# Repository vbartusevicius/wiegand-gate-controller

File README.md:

# Wiegand Gate Controller (`wiegand-gate-controller`)

Compact **ESP32-C6** Wiegand access-control gateway for sliding/swing gates and doors — connects standard 12 V Wiegand card/UHF/keypad readers to gate controllers, door strikes, maglocks, and **Home Assistant** over Wi-Fi/MQTT.

## Enclosure & Hardware (`v1`)

*3D-printed enclosure (`78.8 × 58.8 × 27.7 mm`) with engraved terminal labels and translucent `0.4 mm` status LED windows.*

| 4-Layer PCB — Top (`74.0 × 54.0 mm`) | 4-Layer PCB — Bottom |
| :---: | :---: |
|  |  |

- **9–32 V DC input (`PWR`)**: polyfuse, reverse-polarity diode, TVS clamp, ADC supply monitor, and dual step-down converters (`+5 V` logic + fused `+12 V` reader/aux supply).
- **Wiegand reader port (`WIEGAND`)**: 5 V-tolerant Schmitt-buffered `D0`/`D1`, open-drain `LED`/`BEEP` outputs, supports auto-detected 26/34/37/58-bit cards and 4/8-bit keypad PINs.
- **2× isolated relays (`RELAY 1`, `RELAY 2`)**: potential-free Form-C dry contacts (`2 A / 30 V DC` max) for Open/Close, Step/Pedestrian, or Dual-Door control.
- **3× opto-isolated inputs (`SENSORS`, `EXIT / 12V`)**: accept 5–24 V DC signals or dry contacts (magnetic reed, dual limits, controller blinking status output, and exit/REX pushbutton).
- **Tool-free WAGO 2086 SMD push-in terminals** (`J1`–`J5`, 3.5 mm pitch) + **Seeed XIAO ESP32-C6** (built-in antenna + optional external stickable U.FL antenna via `ANT` exit slot with automatic firmware RSSI selection), dual `WS2812B` RGB LEDs (`NET`, `GATE`), and `RST` button behind a `0.4 mm` translucent cover window.

## Web UI & Home Assistant

### Overview & Live I/O

### Visual Gate Setup & Terminal Map

### Firmware OTA & Maintenance

- **Standalone local access control**: stores up to 500 users/cards/PINs on flash with one-click enrollment of the last unknown scanned tag.
- **Visual setup**: tap how a card read operates your gate/door and how open/closed position is sensed; the live terminal diagram updates to match the labels engraved on the box.
- **Separated Network & OTA pages**: dedicated Wi-Fi + MQTT / Home Assistant auto-discovery tab (`cover` / `lock`, `binary_sensor`, `sensor`, `button`) and drag-and-drop `firmware.bin` OTA updates (gzip-embedded Web UI updates atomically with firmware).

## Enclosure Terminal Map

| Edge | Box Group | Pins | Function |
| :--- | :--- | :--- | :--- |
| Bottom | `PWR` | `V+`, `GND` | 9–32 V DC input |
| Bottom | `WIEGAND` | `12V`, `GND`, `D0`, `D1`, `LED`, `BEEP` | 12 V Wiegand reader & keypad |
| Top | `RELAY 1` | `NC`, `NO`, `COM` | Primary relay dry contact |
| Top | `RELAY 2` | `NC`, `NO`, `COM` | Secondary / Close / Pedestrian relay |
| Top | `SENSORS` | `IN2-`, `IN2+`, `IN1-`, `IN1+` | Position / limit / status inputs |
| Top | `EXIT / 12V` | `GND`, `+12V`, `IN3-`, `IN3+` | Exit (REX) input & +12 V wetting supply |
| Left | `USB` | USB-C | Initial flashing & serial console |
| Right | `ANT` | U.FL coax slot | Optional external 2.4 GHz stickable antenna exit |

## Documentation

- [Wiring & Controller Integration Guide](docs/wiring.md)
- [PCB, BOM & 3D Enclosure Ordering Guide](docs/ordering.md)

## Quick Build & Verification (Docker-first)

```bash
# Python lint
docker compose --profile lint run --rm -T lint check .

# Firmware native & sanitized unit tests + ESP32-C6 release image
docker compose --profile lint run --rm -T cpp-lint "pio test -d firmware -e native && pio test -d firmware -e native_sanitized"
python3 firmware/scripts/release_firmware.py

# Hardware PCB DRC/connectivity + JLCPCB release + tests
docker compose --profile hardware run --rm -T -e JLC_LIVE=0 eda "python3 hardware/scripts/release.py v1 && python3 -m pytest hardware/tests -q -p no:cacheprovider"

# Mechanical enclosure build + tests
docker compose --profile hardware run --rm -T cad "python3 hardware/scripts/build.py --in-cad --test"

# Package GitHub Release bundle (hardware zip + firmware bins + SHA256SUMS.txt + release table)
python3 scripts/package_release.py
```

## License

See [LICENSE.md](LICENSE.md).

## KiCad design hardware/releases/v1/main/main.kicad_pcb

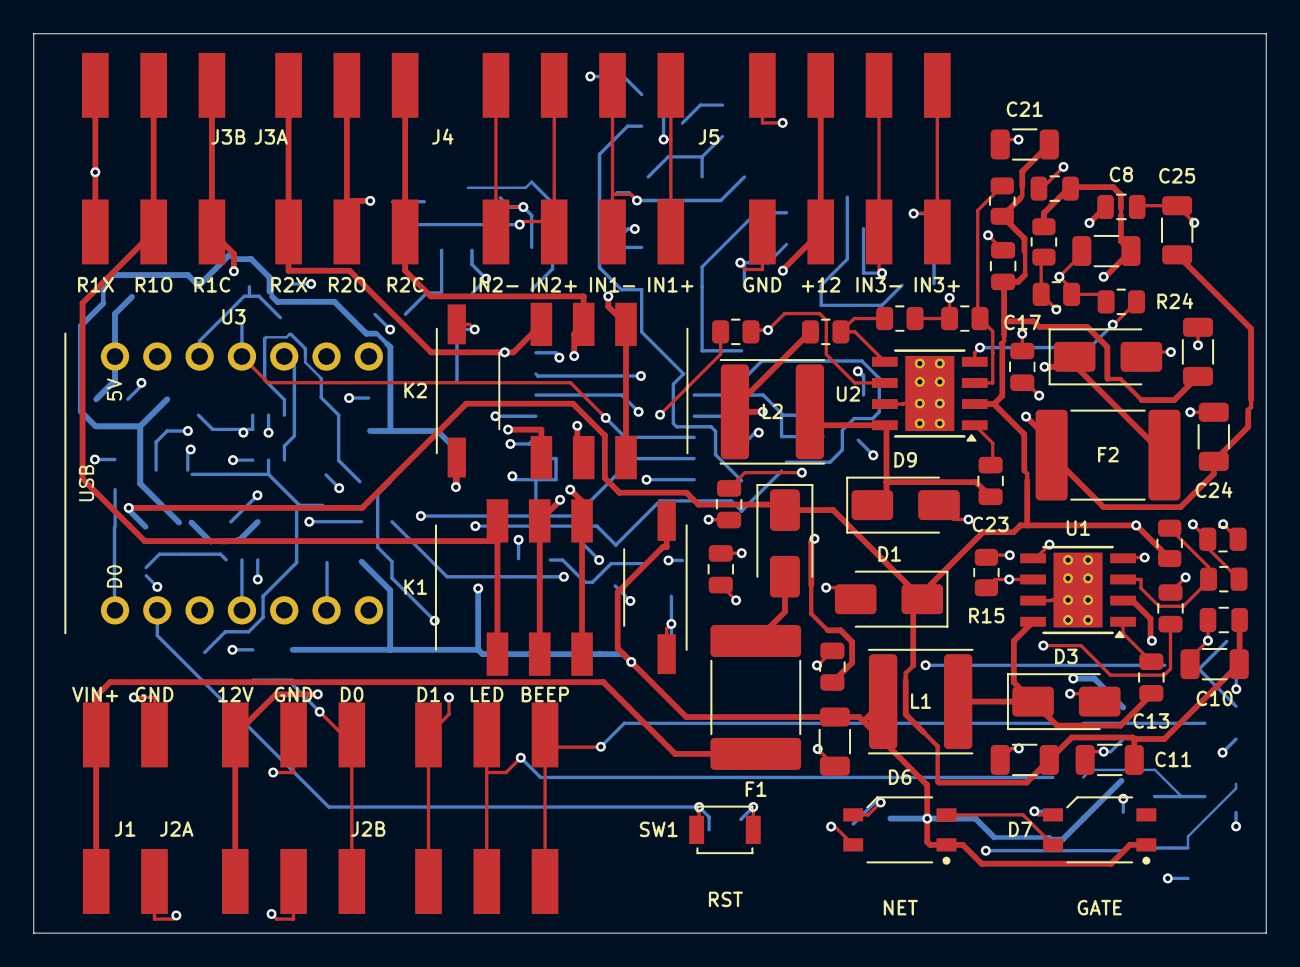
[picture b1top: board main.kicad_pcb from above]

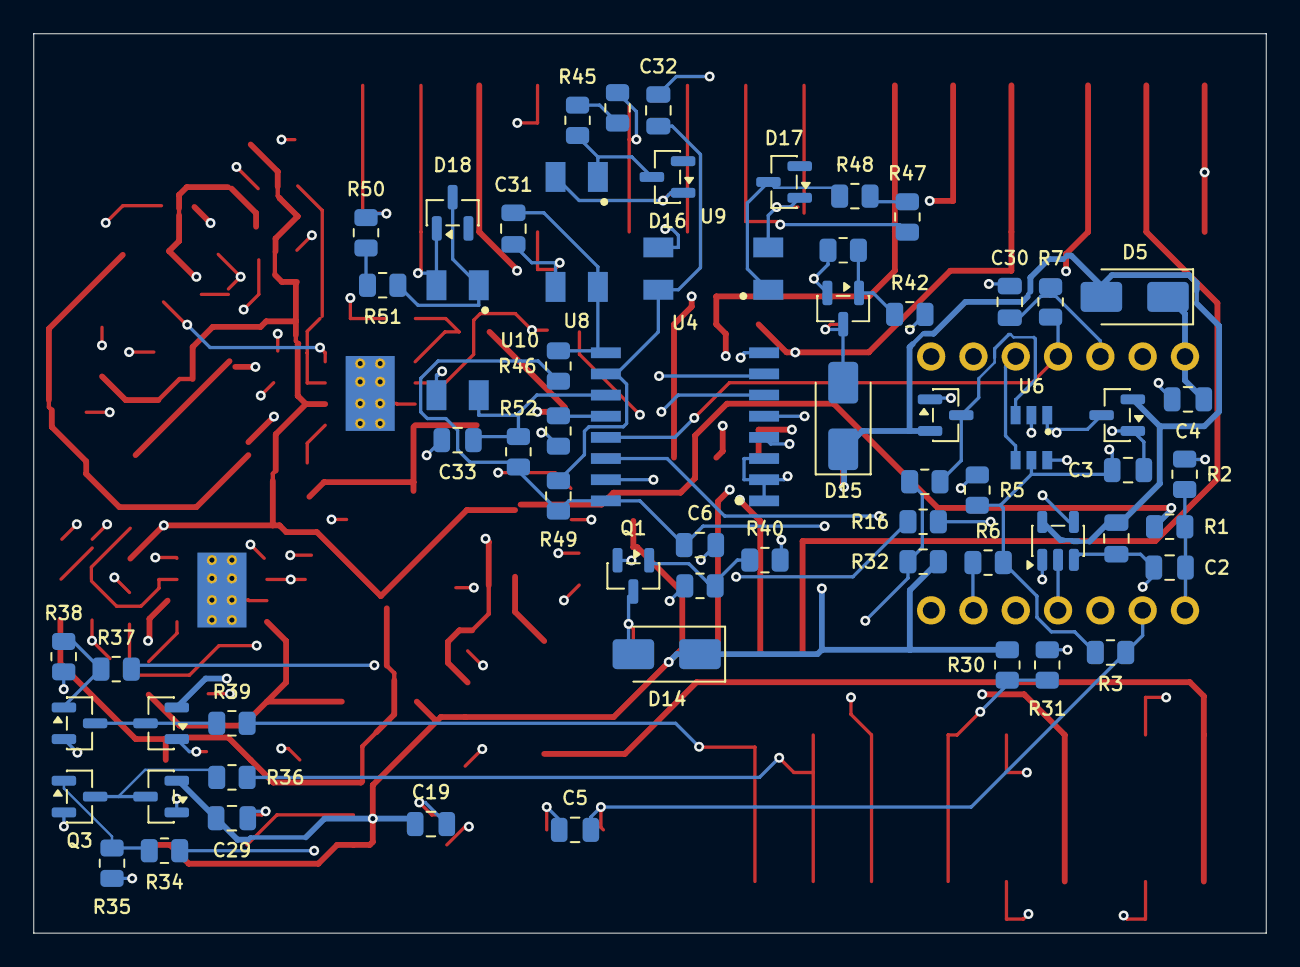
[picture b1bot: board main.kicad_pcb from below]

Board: 4 copper layers, 74.0 x 54.0 mm, 119 parts (63 on the bottom side), 74 nets.

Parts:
C1, C10, C11, C20, C21: 2u2 100V; C_1206_3216Metric
C2, C5, C6, C8, C9, C13, C16, C19, C23, C26, C29, C30, C31, C32, C33: 100n 50V; C_0805_2012Metric
C3, C4: 10u 10V; C_0805_2012Metric
C12, C22: 100n 100V; C_0805_2012Metric
C14, C15: 47u 10V; C_1206_3216Metric
C17: 33n 50V; C_0805_2012Metric
C18, C28: 68p C0G 50V; C_0805_2012Metric
C24, C25: 22u 25V; C_1206_3216Metric
C27: 18n 50V; C_0805_2012Metric
D1: SMAJ36A; D_SMA
D2: SS36; D_SMA
D3, D9: B360A; D_SMA
D5, D14, D15: SS14; D_SMA
D6, D7: WS2812B-MINI-V3J; LED_WS2812B-MINI-V3J
D8: SMAJ15A; D_SMA
D10, D11, D12, D13, D16, D17, D18: BAT54S; SOT-23
F1, F2: 1.1A; Fuse_2920_7451Metric
J1: PWR; TerminalBlock_WAGO_2086-1202_SMD
J2A: WIEGAND_A; TerminalBlock_WAGO_2086-1203_SMD
J2B: WIEGAND_B; TerminalBlock_WAGO_2086-1203_SMD
J3A: RELAY_1; TerminalBlock_WAGO_2086-1203_SMD
J3B: RELAY_2; TerminalBlock_WAGO_2086-1203_SMD
J4: SENSE_1_2; TerminalBlock_WAGO_2086-1204_SMD
J5: SENSE_3_AUX; TerminalBlock_WAGO_2086-1204_SMD
K1, K2: G6S-2F DC5; Relay_DPDT_Omron_G6S-2F_2A
L1: 8.2uH; L_Sunlord_SWPA6045S
L2: 22uH; L_Sunlord_SWPA6045S
Q1, Q2, Q3, Q4: MMBT3904; SOT-23
R1: 100k; R_0805_2012Metric
R2, R3, R4, R7, R23, R30, R32, R35, R38, R41, R43, R46, R49, R52: 10k; R_0805_2012Metric
R5, R6, R44, R45, R47, R48, R50, R51: 2k2; R_0805_2012Metric
R10, R20: 511k; R_0805_2012Metric
R11, R21: 82k5; R_0805_2012Metric
R12, R15, R25: 53k6; R_0805_2012Metric
R13: 10k2; R_0805_2012Metric
R14, R24: 130k; R_0805_2012Metric
R16, R31, R33, R36, R39: 330R; R_0805_2012Metric
R22: 140k; R_0805_2012Metric
R34, R37: 1k; R_0805_2012Metric
R40, R42: 470R; R_0805_2012Metric
SW1: RESTART; SW_SPST_B3U-1000P
U1, U2: TPS54360DDAR; TI_SO-PowerPAD-8_ThermalVias
U3: XIAO ESP32C6; XIAO_ESP32C6_Header
U4: TCA9534DWR; TI_TCA9534DWR_SOIC-16
U5: 74AHCT1G125; SOT-23-5
U6: SN74LVC2G17; TI_SN74LVC2G17_SOT-23-6
U8, U9, U10: EL357N; Everlight_EL357N_SOP-4

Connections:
5V_BST: C13.1, U1.1
5V_CC: C17.1, R15.2
5V_COMP: C18.1, R15.1, U1.6
5V_EN: R10.2, R11.1, U1.3
5V_FB: R12.2, R13.1, U1.5
5V_RT: R14.1, U1.4
5V_SW: C13.2, D3.1, L1.1, U1.8
12V_BST: C23.1, U2.1
12V_CC: C27.1, R25.2
12V_COMP: C28.1, R25.1, U2.6
12V_EN: R20.2, R21.1, U2.3
12V_FB: R22.2, R23.1, U2.5
12V_RT: R24.1, U2.4
12V_SW: C23.2, D9.1, L2.1, U2.8
+3V3: C3.1, C6.1, C30.1, R3.1, R5.1, R6.1, R7.1, R46.1, R49.1, R52.1, U3.12, U4.16, U6.5
+5V: C9.1, C14.1, C15.1, C16.1, C19.1, C29.1, D5.2, D6.1, D7.1, D10.2, D11.2, D12.2, D13.2, D14.1, D15.1, K1.1, K2.1, L1.2, R12.1, R30.1, R32.1, U5.5
+5V_XIAO: C4.1, D5.1, U3.14
+12V_RDR: C24.1, C25.1, C26.1, F2.1, L2.2, R22.1
+12V_RDR_OUT: C8.1, D8.1, F2.2, J2A.1, J5.3
BTN_RESTART: C5.1, R3.2, SW1.1, U3.2
EXP_INT: R7.2, U3.11, U4.13
EXP_P7: R4.1, U4.12
GND: C1.2, C2.2, C3.2, C4.2, C5.2, C6.2, C8.2, C9.2, C10.2, C11.2, C12.2, C14.2, C15.2, C16.2, C17.2, C18.2, C19.2, C20.2, C21.2, C22.2, C24.2, C25.2, C26.2, C27.2, C28.2, C29.2, C30.2, C31.2, C32.2, C33.2, D1.2, D3.2, D6.3, D7.3, D8.2, D9.2, D10.1, D11.1, D12.1, D13.1, J1.2, J2A.2, J5.4, Q1.2, Q2.2, Q3.2, Q4.2, R2.2, R4.2, R11.2, R13.2, R14.2, R21.2, R23.2, R24.2, R35.2, R38.2, R41.2, R43.2, SW1.2, U1.7, U1.9, U2.7, U2.9, U3.13, U4.1, U4.2, U4.3, U4.8, U5.1, U5.3, U6.2, U8.3, U9.3, U10.3
I2C_SCL: R6.2, U3.6, U4.14
I2C_SDA: R5.2, U3.5, U4.15
IN1_LED_A: D16.3, R45.2, U8.1
IN1_MCU: C31.1, R46.2, U4.9, U8.4
IN1_MID: R44.2, R45.1
IN1_N: D16.1, J4.2, U8.2
IN1_P: J4.1, R44.1
IN2_LED_A: D17.3, R48.2, U9.1
IN2_MCU: C32.1, R49.2, U4.10, U9.4
IN2_MID: R47.2, R48.1
IN2_N: D17.1, J4.4, U9.2
IN2_P: J4.3, R47.1
IN3_LED_A: D18.3, R51.2, U10.1
IN3_MCU: C33.1, R52.2, U4.11, U10.4
IN3_MID: R50.2, R51.1
IN3_N: D18.1, J5.2, U10.2
IN3_P: J5.1, R50.1
LED_BUF: R16.1, U5.4
LED_CHAIN1: D6.2, D7.4
LED_DATA: U3.4, U5.2
LED_DIN: D6.4, R16.2
R1_BASE: Q1.1, R40.2, R41.1
R1_COIL_N: D14.2, K1.12, Q1.3
R1_COM: J3A.1, K1.4, K1.9
R1_NC: J3A.3, K1.3, K1.10
R1_NO: J3A.2, K1.5, K1.8
R2_BASE: Q2.1, R42.2, R43.1
R2_COIL_N: D15.2, K2.12, Q2.3
R2_COM: J3B.1, K2.4, K2.9
R2_NC: J3B.3, K2.3, K2.10
R2_NO: J3B.2, K2.5, K2.8
RELAY1_DRV: R40.1, U4.4
RELAY2_DRV: R42.1, U4.5
VIN_ADC: C2.1, R1.2, R2.1, U3.1
VIN_FUSED: D2.2, F1.2
VIN_PROT: C1.1, C10.1, C11.1, C12.1, C20.1, C21.1, C22.1, D1.1, D2.1, R1.1, R10.1, R20.1, U1.2, U2.2
VIN_RAW: F1.1, J1.1
WG_BEEP_BASE: Q4.1, R37.2, R38.1
WG_BEEP_COL: D13.3, Q4.3, R39.1
WG_BEEP_DRV: R37.1, U4.7
WG_BEEP_TERM: J2B.3, R39.2
WG_D0_IN: D10.3, R31.2, U6.1
WG_D0_MCU: U3.3, U6.6
WG_D0_TERM: J2A.3, R30.2, R31.1
WG_D1_IN: D11.3, R33.2, U6.3
WG_D1_MCU: U3.10, U6.4
WG_D1_TERM: J2B.1, R32.2, R33.1
WG_LED_BASE: Q3.1, R34.2, R35.1
WG_LED_COL: D12.3, Q3.3, R36.1
WG_LED_DRV: R34.1, U4.6
WG_LED_TERM: J2B.2, R36.2

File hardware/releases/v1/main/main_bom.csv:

Line,Qty,Designators,Value,Package,Type,Manufacturer,MPN,LCSC,Assembly
1,5,"C1,C10,C11,C20,C21",2u2 100V,C_1206_3216Metric,SMD,Samsung,CL31B225KCHSNNE,C170101,machine
2,2,"C12,C22",100n 100V,C_0805_2012Metric,SMD,YAGEO,CC0805KKX7R0BB104,C106243,machine
3,15,"C13,C16,C19,C2,C23,C26,C29,C30,C31,C32,C33,C5,C6,C8,C9",100n 50V,C_0805_2012Metric,SMD,YAGEO,CC0805KRX7R9BB104,C49678,machine
4,2,"C14,C15",47u 10V,C_1206_3216Metric,SMD,Samsung,CL31A476MPHNNNE,C96123,machine
5,1,C17,33n 50V,C_0805_2012Metric,SMD,YAGEO,CC0805KRX7R9BB333,C107150,machine
6,2,"C18,C28",68p C0G 50V,C_0805_2012Metric,SMD,YAGEO,CC0805JRNPO9BN680,C107120,machine
7,2,"C24,C25",22u 25V,C_1206_3216Metric,SMD,Samsung,CL31A226KAHNNNE,C12891,machine
8,1,C27,18n 50V,C_0805_2012Metric,SMD,YAGEO,CC0805JRX7R9BB183,C520032,machine
9,2,"C3,C4",10u 10V,C_0805_2012Metric,SMD,Samsung,CL21A106KPFNNNE,C17024,machine
10,1,D1,SMAJ36A,D_SMA,SMD,MDD,SMAJ36A,C113967,machine
11,7,"D10,D11,D12,D13,D16,D17,D18",BAT54S,SOT-23,SMD,Nexperia,"BAT54S,215",C47546,machine
12,3,"D14,D15,D5",SS14,D_SMA,SMD,MDD,SS14,C2480,machine
13,1,D2,SS36,D_SMA,SMD,MDD,SS36,C16015,machine
14,2,"D3,D9",B360A,D_SMA,SMD,Diodes Inc,B360A-13-F,C94193,machine
15,2,"D6,D7",WS2812B-MINI-V3J,LED_WS2812B-MINI-V3J,SMD,Worldsemi,WS2812B-MINI-V3J,C22371519,machine
16,1,D8,SMAJ15A,D_SMA,SMD,Littelfuse,SMAJ15A,C148216,machine
17,2,"F1,F2",1.1A,Fuse_2920_7451Metric,SMD,Littelfuse,2920L110/60V,C49318488,machine
18,1,J1,PWR,TerminalBlock_WAGO_2086-1202_SMD,SMD,WAGO,2086-1202/700-000/997-604,,hand-fit
19,1,J2A,WIEGAND_A,TerminalBlock_WAGO_2086-1203_SMD,SMD,WAGO,2086-1203/700-000/997-605,C3309626,machine
20,1,J2B,WIEGAND_B,TerminalBlock_WAGO_2086-1203_SMD,SMD,WAGO,2086-1203/700-000/997-605,C3309626,machine
21,1,J3A,RELAY_1,TerminalBlock_WAGO_2086-1203_SMD,SMD,WAGO,2086-1203/700-000/997-605,C3309626,machine
22,1,J3B,RELAY_2,TerminalBlock_WAGO_2086-1203_SMD,SMD,WAGO,2086-1203/700-000/997-605,C3309626,machine
23,1,J4,SENSE_1_2,TerminalBlock_WAGO_2086-1204_SMD,SMD,WAGO,2086-1204/700-000/997-605,C3309718,machine
24,1,J5,SENSE_3_AUX,TerminalBlock_WAGO_2086-1204_SMD,SMD,WAGO,2086-1204/700-000/997-605,C3309718,machine
25,2,"K1,K2",G6S-2F DC5,Relay_DPDT_Omron_G6S-2F_2A,SMD,Omron,G6S-2F DC5,C16707,machine
26,1,L1,8.2uH,L_Sunlord_SWPA6045S,SMD,APV,ANR6045T8R2M,C7427168,machine
27,1,L2,22uH,L_Sunlord_SWPA6045S,SMD,Bourns,SRN6045TA-220M,C2044314,machine
28,4,"Q1,Q2,Q3,Q4",MMBT3904,SOT-23,SMD,CJ,MMBT3904(RANGE:100-300),C20526,machine
29,1,R1,100k,R_0805_2012Metric,SMD,UNI-ROYAL,0805W8F1003T5E,C149504,machine
30,2,"R10,R20",511k,R_0805_2012Metric,SMD,UNI-ROYAL,0805W8F5113T5E,C17735,machine
31,2,"R11,R21",82k5,R_0805_2012Metric,SMD,YAGEO,RC0805FR-0782K5L,C276314,machine
32,3,"R12,R15,R25",53k6,R_0805_2012Metric,SMD,UNI-ROYAL,0805W8F5362T5E,C21398,machine
33,1,R13,10k2,R_0805_2012Metric,SMD,UNI-ROYAL,0805W8F1022T5E,C17402,machine
34,2,"R14,R24",130k,R_0805_2012Metric,SMD,UNI-ROYAL,0805W8F1303T5E,C17450,machine
35,5,"R16,R31,R33,R36,R39",330R,R_0805_2012Metric,SMD,UNI-ROYAL,0805W8F3300T5E,C17630,machine
36,14,"R2,R23,R3,R30,R32,R35,R38,R4,R41,R43,R46,R49,R52,R7",10k,R_0805_2012Metric,SMD,UNI-ROYAL,0805W8F1002T5E,C17414,machine
37,1,R22,140k,R_0805_2012Metric,SMD,UNI-ROYAL,0805W8F1403T5E,C17460,machine
38,2,"R34,R37",1k,R_0805_2012Metric,SMD,UNI-ROYAL,0805W8F1001T5E,C17513,machine
39,2,"R40,R42",470R,R_0805_2012Metric,SMD,UNI-ROYAL,0805W8F4700T5E,C17710,machine
40,8,"R44,R45,R47,R48,R5,R50,R51,R6",2k2,R_0805_2012Metric,SMD,UNI-ROYAL,0805W8F2201T5E,C17520,machine
41,1,SW1,RESTART,SW_SPST_B3U-1000P,SMD,Omron,B3U-1000P,C231329,machine
42,2,"U1,U2",TPS54360DDAR,TI_SO-PowerPAD-8_ThermalVias,SMD,Texas Instruments,TPS54360DDAR,C44377,machine
43,3,"U10,U8,U9",EL357N,Everlight_EL357N_SOP-4,SMD,Everlight,EL357N(C)(TA)-G,C42379244,machine
44,1,U3,XIAO ESP32C6,XIAO_ESP32C6_Header,THT,Seeed Studio,102010636,,hand-fit
45,1,U4,TCA9534DWR,TI_TCA9534DWR_SOIC-16,SMD,TI,TCA9534DWR,C2870609,machine
46,1,U5,74AHCT1G125,SOT-23-5,SMD,TI,SN74AHCT1G125DBVR,C7484,machine
47,1,U6,SN74LVC2G17,TI_SN74LVC2G17_SOT-23-6,SMD,UMW,SN74LVC2G17DBVR(UMW),C7394037,machine

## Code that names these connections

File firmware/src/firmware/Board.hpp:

#pragma once

#include <cstddef>
#include <cstdint>

#include "firmware/EspIdfHostStubs.hpp"

// Seeed XIAO ESP32-C6 pin assignment on Wiegand Gate Controller v1 main board:
//   D0  / GPIO0  = VIN_ADC     (ADC1_CH0: 9-32 V DC input monitor via 100k/10k divider)
//   D1  / GPIO1  = BTN_RESTART (SW1 Restart / AP Setup / Factory Reset button, active LOW)
//   D2  / GPIO2  = WG_D0       (Wiegand Data 0 via 5V-tolerant Schmitt buffer, falling edge)
//   D3  / GPIO21 = LED_DATA    (2x WS2812B-MINI-V3J RGB LEDs via 74AHCT1G125 buffer)
//   D4  / GPIO22 = I2C_SDA     (PCA9534 8-bit I/O expander @ 0x20)
//   D5  / GPIO23 = I2C_SCL     (I2C clock, 400 kHz)
//   D9  / GPIO20 = WG_D1       (Wiegand Data 1 via 5V-tolerant Schmitt buffer, falling edge)
//   D10 / GPIO18 = EXP_INT     (PCA9534 /INT active LOW)
namespace gateway {
namespace firmware {
namespace board {

constexpr gpio_num_t boot_btn_pin = GPIO_NUM_9;

constexpr gpio_num_t vin_adc_pin = GPIO_NUM_0;
constexpr adc_channel_t vin_adc_channel = ADC_CHANNEL_0;

constexpr gpio_num_t btn_restart_pin = GPIO_NUM_1;
constexpr gpio_num_t wg_d0_pin = GPIO_NUM_2;
constexpr gpio_num_t led_data_pin = GPIO_NUM_21;
constexpr gpio_num_t i2c_sda_pin = GPIO_NUM_22;
constexpr gpio_num_t i2c_scl_pin = GPIO_NUM_23;
constexpr gpio_num_t wg_d1_pin = GPIO_NUM_20;
constexpr gpio_num_t exp_int_pin = GPIO_NUM_18;

// Seeed XIAO ESP32-C6 internal FM8625H RF switch (selects external U.FL flex dipole antenna):
constexpr gpio_num_t rf_switch_power_pin = GPIO_NUM_3;
constexpr gpio_num_t rf_antenna_select_pin = GPIO_NUM_14;
constexpr std::int8_t wifi_max_tx_power_quarter_dbm = 82;

constexpr std::uint8_t i2c_addr_pca9534 = 0x20;
constexpr std::uint32_t i2c_speed_hz = 400000;
constexpr float vin_divider_ratio = 11.0F;  // 100k / 10k

// PCA9534 bit assignments
constexpr std::uint8_t exp_bit_relay1 = 0;
constexpr std::uint8_t exp_bit_relay2 = 1;
constexpr std::uint8_t exp_bit_wg_led = 2;
constexpr std::uint8_t exp_bit_wg_beep = 3;
constexpr std::uint8_t exp_bit_in1 = 4;
constexpr std::uint8_t exp_bit_in2 = 5;
constexpr std::uint8_t exp_bit_in3 = 6;

constexpr bool usb_pin(gpio_num_t pin) {
    return pin == GPIO_NUM_12 || pin == GPIO_NUM_13;
}

constexpr bool pins_distinct() {
    const gpio_num_t pins[] = {
        vin_adc_pin, btn_restart_pin, wg_d0_pin,   led_data_pin,        i2c_sda_pin,
        i2c_scl_pin, wg_d1_pin,       exp_int_pin, rf_switch_power_pin, rf_antenna_select_pin,
    };
    for (std::size_t i = 0; i < sizeof(pins) / sizeof(pins[0]); ++i) {
        if (usb_pin(pins[i])) {
            return false;
        }
        for (std::size_t j = i + 1; j < sizeof(pins) / sizeof(pins[0]); ++j) {
            if (pins[i] == pins[j]) {
                return false;
            }
        }
    }
    return true;
}

static_assert(pins_distinct(), "Wiegand Gate Controller pins must be distinct and avoid USB D-/D+");

}  // namespace board
}  // namespace firmware
}  // namespace gateway
